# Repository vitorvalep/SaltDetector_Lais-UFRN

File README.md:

# SaltDetector_Lais-UFRN

Projeto foi feito como parte da seleção para bolsista do Laboratório de Inovação Tecnológica em Saúde.
Este projeto consiste em um hardware capaz de identificar a presença de sal ou açúcar em água. Para isso o projeto foi dividido em 4 partes

1 - Simulação de parte do projeto utilizando a ferramenta tinkerCAD e plataforma arduino

2 - Codificação do firmware utilizando a plataforma Arduino

3 - Desenvolvimento do hardware utilizando a ferramenta da autodesk Eagle.

4 - Desenvolvimento de case de proteção do hardware

## O projeto da placa de circuito impresso contém:

1 - Microcontrolador atmega328p, sendo o cérebro do sistema.

2 - Amplificadores operacionais para amplificação do sinal medido pelos eletrodos. Estes circuitos devem ser alterados durante calibração e testes.

3 - Suporte para cartão SD para que os dados sejam salvos em csv para análises posteriores.

4 - RTC para manter o horário atualizado e fazer o controle dos arquivos salvos no SD card

5 - Sistema de carregamento e utilização de baterias do tipo Lithium ion.

6 - Sensor de corrente I²C para medição de corrente para medição de corrente nos eletrodos.

7 - Display LCD 16x2 para visualização de informações dos sensores.

O Hardware desenvolvido é capaz de medir a condutividade da água por meio de uma célula formada por 3 eletrodos. Para a medição da condutividade, utilizou-se amplificadores operacionais para amplificar o sinal medido pelos eletrodos. A informação de que existe sal ou açúcar na água se dá por meio de um lcd 16x2, que mostra a condutividade da água e se há sal ou açúcar no mesmo. O dispositivo funciona com bateria do tipo Lithium ion e pode ser recarregado por uma entrada micro USB.

O dispositivo também é capaz de realizar a voltametria cíclica, experimento que consiste em enviar uma onda triangular de tensão e observar os valores de tensão e corrente nos eletrodos da célula Por meio do sensor de corrente embutido no hardware pode-se medir a corrente que flui pelo eletrodo de trabalho e o conversor A/D do chip atmeg328p junto com os amplificadores operacionais obtém o valor da tensão sobre o eletrodo de referência e o eletrodo de trabalho. Após a varredura, duas informações são mostradas no LCD, que são os picos de corrente e tensão durante o experimento. Há um slot para cartão SD que guarda todos os valores em um arquivo csv, cujo nome é a data e horário da voltametria. Com esse arquivo pode-se exportar as informações e gerar gráficos para análises posteriores

## Melhorias para o projeto.

1 - Utilizar de um display TFT touch para plotar gráficos e mostrar mais informações sobre a voltametria cíclica, bem como melhorar a interação entre o operador e hardware

2 - Utilizar um chip de comunicação GSM para que os dados sejam enviados em tempo real para a nuvem e lá contenha todas as informações coletadas pelo operador, eliminando assim, o uso do cartão SD.

3 - Melhorias do case de proteção da placa

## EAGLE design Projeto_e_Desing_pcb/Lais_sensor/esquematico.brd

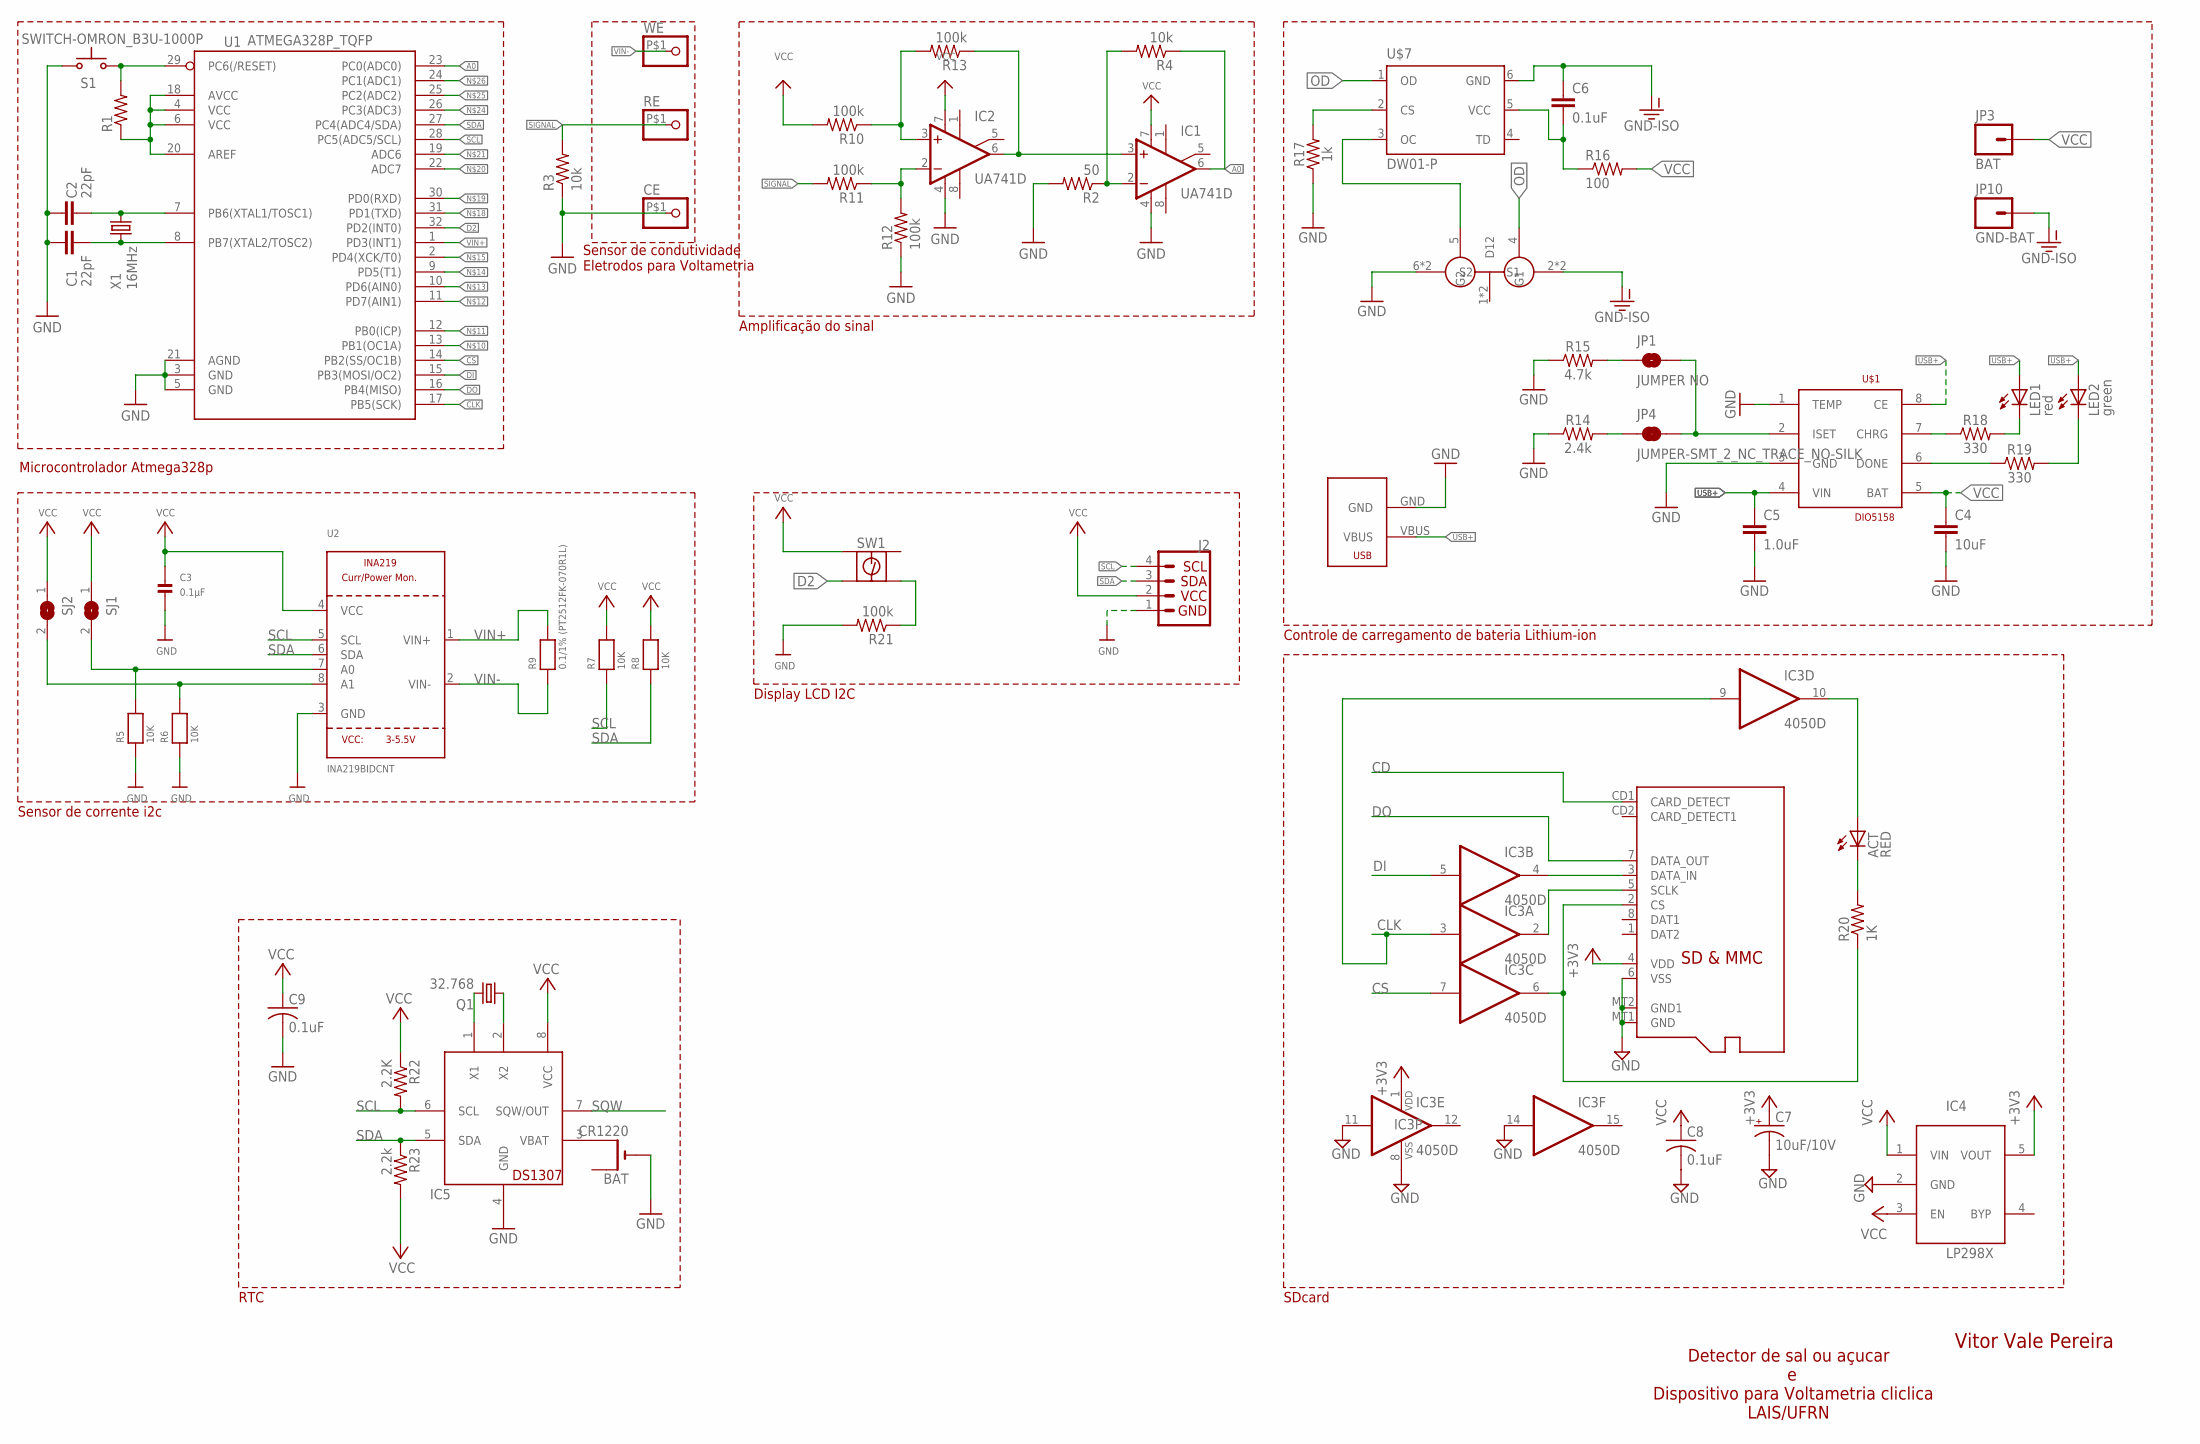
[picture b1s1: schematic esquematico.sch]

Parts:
ACT: RED; CHIP-LED0805
BAT: CR1220; CR1220-THM
C1, C2: 22pF; CAPM6032X280
C3: 0.1µF; 0805
C4: 10uF; 1206
C5: 1.0uF; 0603
C6: 0.1uF; 0603
C7: 10uF/10V; A/3216-18R
C8: 0.1uF; C0805K
C9: 0.1uF; C025-025X050
CE: PINHD-1X1-BIGPOGO; 1X1-BIGPOGO
IC1, IC2: UA741D; SO08
IC3: 4050D; SO16
IC4: LP298XS; SOT23-5L
IC5: DS1307; DIL08
J2: I2C_STANDARD; 1X04
JP1: JUMPER NO; SMT-JUMPER_2_NO_NO-SILK
JP3: BAT; 1X01
JP4: JUMPER-SMT_2_NC_TRACE_NO-SILK; SMT-JUMPER_2_NC_TRACE_NO-SILK
JP10: GND-BAT; 1X01
LED1: red; CHIP-LED0805
LED2: green; CHIP-LED0805
Q1: 32.768; TC38H
R1: R-US_R0805; R0805
R2: 50; R0805
R3, R4: 10k; R0805
R5, R6, R7, R8: 10K; 0805
R9: 0.1/1% (PT2512FK-070R1L); 2512
R10, R11, R12, R13, R21: 100k; R0805
R14: 2.4k; 0603
R15: 4.7k; 0603
R16: 100; 0603-RES
R17: 1k; 0603
R18, R19: 330; 0603
R20: 1K; R0805
R22: 2.2K; 0207/10
R23: 2.2k; 0207/10
RE: PINHD-1X1-BIGPOGO; 1X1-BIGPOGO
S1: SWITCH-OMRON_B3U-1000P
SJ1, SJ2: SOLDERJUMPERREFLOW_NOPASTE; SOLDERJUMPER_REFLOW_NOPASTE
SW1: PTS645SM43SMTR92LFS; PTS645-SMT-6MM
U1: ATMEGA328P_TQFP; TQFP32-08
U2: INA219BIDCNT; SOT23-8
U$1: DIO5158; SOIC-8
U$7: DW01-P; SOT23-6L
U$8: FS8205A; TSSOP8
U$9: USB-MICROB-POWERONLY
WE: PINHD-1X1-BIGPOGO; 1X1-BIGPOGO
X1: 16MHz; XTAL_HC49
X2: MICROSD

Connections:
+3V3: C7.+, IC3.1 (VDD), IC4.5 (VOUT), X2.4 (VDD)
A0: IC1.6 (OUT), R4.1, U1.23 (PC0(ADC0))
CD: X2.CD1 (CARD_DETECT)
CHRG: R18.1, U$1.7 (CHRG)
CLK: IC3.3 (I), IC3.9 (I), U1.17 (PB5(SCK))
CS: IC3.7 (I), U1.14 (PB2(SS/OC1B))
D2: SW1.P$3 (3), U1.32 (PD2(INT0))
DI: IC3.5 (I), U1.15 (PB3(MOSI/OC2))
DO: U1.16 (PB4(MISO)), X2.7 (DATA_OUT)
DONE: R19.1, U$1.6 (DONE)
GND: BAT.-, C1.1, C2.1, C3.2, C4.2, C5.2, C7.-, C8.2, C9.2, CE.P$1, IC1.4 (V-), IC2.4 (V-), IC3.8 (VSS), IC3.11 (I), IC3.14 (I), IC4.2 (GND), IC5.4 (GND), J2.1, R2.2, R3.1, R5.1, R6.1, R12.1, R14.1, R15.1, R17.1, R21.2, S1.1, U1.3 (GND), U1.5 (GND), U1.21 (AGND), U2.3 (GND), U$1.1 (TEMP), U$1.3 (GND), U$8.6 (S2), U$8.7 (S2), U$9.GND, X2.6 (VSS), X2.MT1 (GND), X2.MT2 (GND1)
GND-ISO: C6.1, JP10.1, U$7.6 (GND), U$8.2 (S1), U$8.3 (S1)
ISET: JP1.2, JP4.2, U$1.2 (ISET)
LED1: LED1.C, R18.2
LED2: LED2.C, R19.2
unnamed: C2.2, U1.7 (PB6(XTAL1/TOSC1)), X1.2
unnamed: C1.2, U1.8 (PB7(XTAL2/TOSC2)), X1.1
unnamed: R1.2, S1.2 (S), U1.29 (PC6(/RESET))
unnamed: IC1.2 (-IN), R2.1, R4.2
unnamed: R21.1, SW1.P$4 (4)
unnamed: R6.2, SJ2.2, U2.8 (A1)
unnamed: IC5.1 (X1), Q1.2
unnamed: IC2.3 (+IN), R10.1, R13.2
unnamed: IC5.2 (X2), Q1.1
unnamed: IC2.2 (-IN), R11.1, R12.2
unnamed: IC1.3 (+IN), IC2.6 (OUT), R13.1
unnamed: R5.2, SJ1.2, U2.7 (A0)
unnamed: JP4.1, R14.2
unnamed: JP1.1, R15.2
unnamed: R17.2, U$7.2 (CS)
unnamed: U$7.3 (OC), U$8.5 (G2)
unnamed: ACT.A, IC3.10 (O)
unnamed: IC3.2 (O), X2.5 (SCLK)
unnamed: IC3.6 (O), R20.1, X2.2 (CS)
unnamed: ACT.C, R20.2
unnamed: IC3.4 (O), X2.3 (DATA_IN)
unnamed: BAT.+2 (+1), IC5.3 (VBAT)
OD: U$7.1 (OD), U$8.4 (G1)
SCL: IC5.6 (SCL), J2.4, R7.1, R22.2, U1.28 (PC5(ADC5/SCL)), U2.5 (SCL)
SDA: IC5.5 (SDA), J2.3, R8.1, R23.1, U1.27 (PC4(ADC4/SDA)), U2.6 (SDA)
SIGNAL: R3.2, R11.2, RE.P$1
SQW: IC5.7 (SQW/OUT)
USB+: C5.1, LED1.A, LED2.A, U$1.4 (VIN), U$1.8 (CE), U$9.VBUS
VCC: C3.1, C4.1, C8.1, C9.1, IC1.7 (V+), IC2.7 (V+), IC4.1 (VIN), IC4.3 (EN), IC5.8 (VCC), J2.2, JP3.1, R1.1, R7.2, R8.2, R10.2, R16.2, R22.1, R23.2, SJ1.1, SJ2.1, SW1.P$1 (1), U1.4 (VCC), U1.6 (VCC), U1.18 (AVCC), U1.20 (AREF), U2.4 (VCC), U$1.5 (BAT)
VCC-DW: C6.2, R16.1, U$7.5 (VCC)
VIN+: R9.2, U1.1 (PD3(INT1)), U2.1 (VIN+)
VIN-: R9.1, U2.2 (VIN-), WE.P$1

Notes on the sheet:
Sensor de condutividade Eletrodos para Voltametria
Sensor de corrente i2c
Amplificação do sinal
Microcontrolador Atmega328p
Controle de carregamento de bateria Lithium-ion
SDcard
Display LCD I2C
RTC
Vitor Vale Pereira
Detector de sal ou açucar e Dispositivo para Voltametria cliclica LAIS/UFRN

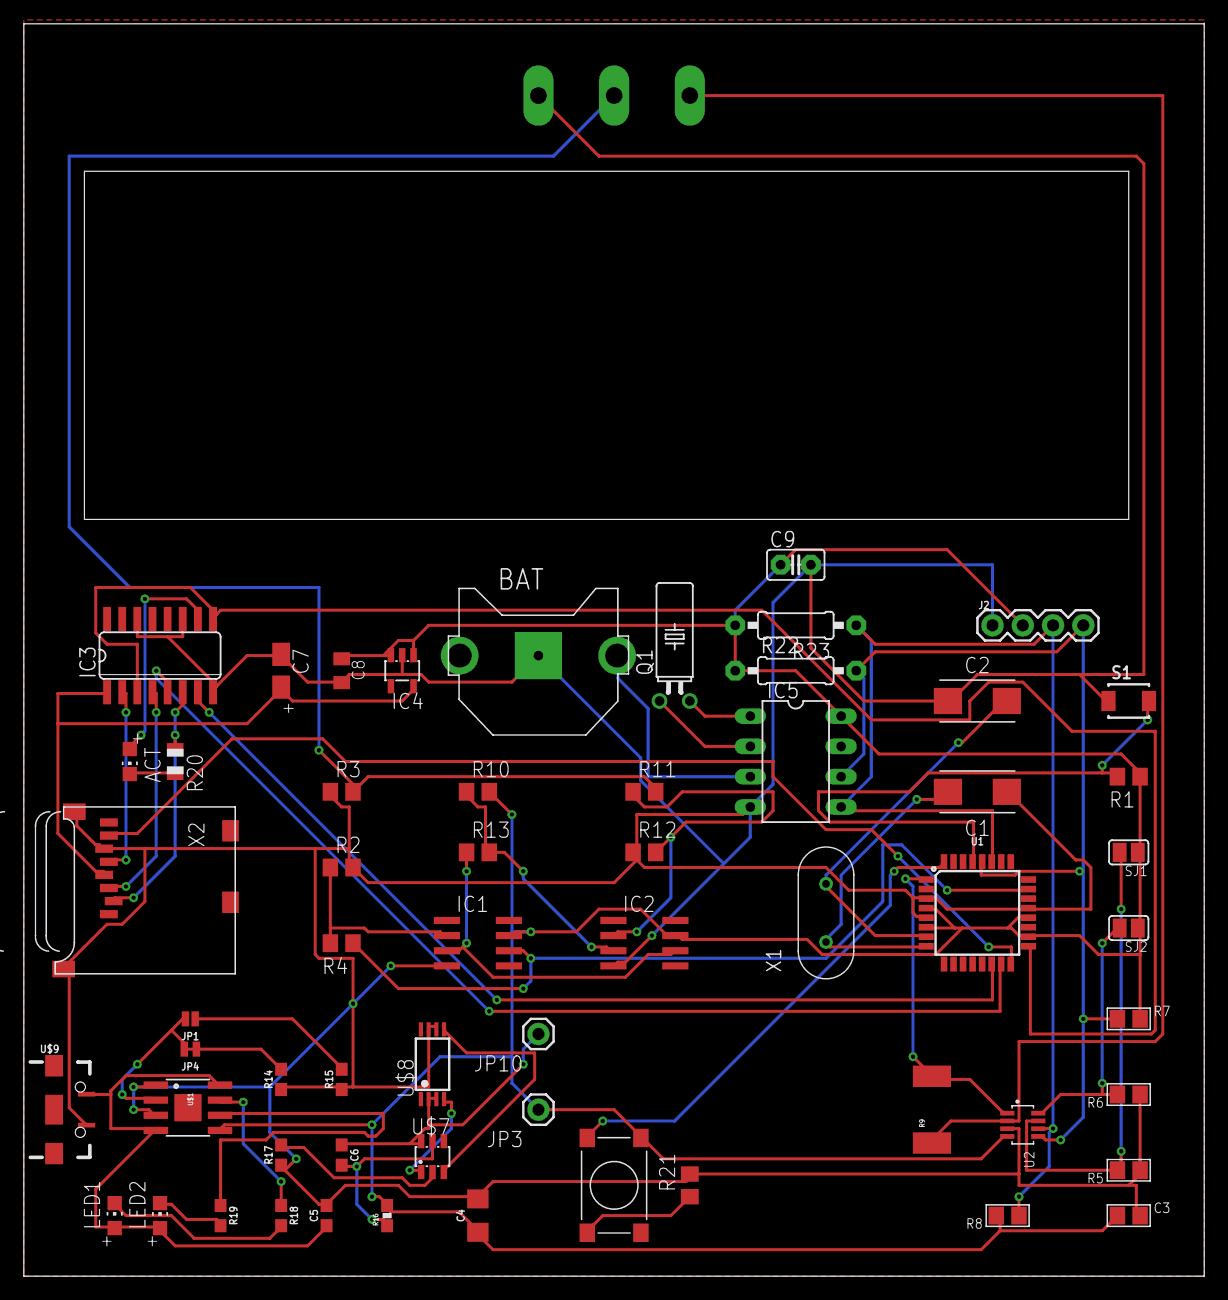
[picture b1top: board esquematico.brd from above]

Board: 2 copper layers, 99.0 x 105.1 mm, 62 parts (0 on the bottom side), 45 nets.

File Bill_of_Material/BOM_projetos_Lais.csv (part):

"Part";"Value";"Device";"Package";"Description";"CATEGORY";"CREATED_BY";"LABEL";"MANUFACTURER";"MPN";"OPERATING_TEMP";"PACKAGE";"PART_STATUS";"POPULARITY";"PROD_ID";"ROHS_COMPLIANT";"SERIES";"SPICEPREFIX";"SUB-CATEGORY";"THERMALLOSS";"TYPE";"VALUE";"VOLTAGE_RATING";
"ACT";"RED";"LEDCHIP-LED0805";"CHIP-LED0805";"LED";"";"";"";"";"";"";"";"";"";"";"";"";"";"";"";"";"";"";
"BAT";"CR1220";"CR1220THM";"CR1220-THM";"CR1216/CR1220/CR1225 12mm 3V lithium coin cell";"";"";"";"";"";"";"";"";"";"";"";"";"";"";"";"";"";"";
"C1";"22pF";"C_TANTALUM-2412(6032-METRIC)";"CAPM6032X280";"Capacitor - Generic";"Capacitor";"";"";"";"";"";"";"";"";"";"";"";"";"";"";"";"";"";
"C2";"22pF";"C_TANTALUM-2412(6032-METRIC)";"CAPM6032X280";"Capacitor - Generic";"Capacitor";"";"";"";"";"";"";"";"";"";"";"";"";"";"";"";"";"";
"C3";"0.1µF";"CAP_CERAMIC0805";"0805";"Ceramic Capacitors";"";"";"";"";"";"";"";"";"";"";"";"";"";"";"";"";"";"";
"C4";"10uF";"10UF-1206-6.3V-20%";"1206";"10.0µF ceramic capacitors";"";"";"";"";"";"";"";"";"";"CAP-10057";"";"";"";"";"";"";"10uF";"";
"C5";"1.0uF";"1.0UF-0603-16V-10%";"0603";"1µF ceramic capacitors";"";"";"";"";"";"";"";"";"";"CAP-00868";"";"";"";"";"";"";"1.0uF";"";
"C6";"0.1uF";"0.1UF-0603-25V-5%";"0603";"0.1µF ceramic capacitors";"";"";"";"";"";"";"";"";"";"CAP-08604";"";"";"";"";"";"";"0.1uF";"";
"C7";"10uF/10V";"CPOL-USA/3216-18R";"A/3216-18R";"POLARIZED CAPACITOR, American symbol";"";"";"";"";"";"";"";"";"";"";"";"";"";"";"";"";"";"";
"C8";"0.1uF";"C-USC0805K";"C0805K";"CAPACITOR, American symbol";"";"";"";"";"";"";"";"";"";"";"";"";"";"";"";"";"";"";
"C9";"0.1uF";"C-US025-025X050";"C025-025X050";"CAPACITOR, American symbol";"";"";"";"";"";"";"";"";"";"";"";"";"";"";"";"";"";"";
"CE";"";"PINHD-1X1-BIGPOGO";"1X1-BIGPOGO";"Pin header 1x1 for 0.1" spacing";"";"";"";"";"";"";"";"";"";"";"";"";"";"";"";"";"";"";
"IC1";"UA741D";"UA741D";"SO08";"OP AMP";"";"";"";"";"";"";"";"";"0";"";"";"";"";"";"";"";"";"";
"IC2";"UA741D";"UA741D";"SO08";"OP AMP";"";"";"";"";"";"";"";"";"0";"";"";"";"";"";"";"";"";"";
"IC3";"4050D";"4050D";"SO16";"Hex non-inverting BUFFER";"";"";"";"";"";"";"";"";"";"";"";"";"";"";"";"";"";"";
"IC4";"LP298XS";"LP298XS";"SOT23-5L";"";"";"";"";"";"";"";"";"";"";"";"";"";"";"";"";"";"";"";
"IC5";"DS1307";"DS1307";"DIL08";"DS1307";"";"";"";"";"";"";"";"";"";"";"";"";"";"";"";"";"";"";
"J2";"";"I2C_STANDARD";"1X04";"SparkFun I2C Standard Pinout Header";"";"";"";"";"";"";"";"";"";"";"";"";"";"";"";"";"";"";
"JP1";"JUMPER NO";"JUMPER-SMT_2_NO_NO-SILK";"SMT-JUMPER_2_NO_NO-SILK";"Normally open jumper";"";"";"";"";"";"";"";"";"";"";"";"";"";"";"";"";"";"";
"JP3";"BAT";"M01PTH";"1X01";"Header 1";"";"";"";"";"";"";"";"";"";"";"";"";"";"";"";"";"";"";
"JP4";"JUMPER-SMT_2_NC_TRACE_NO-SILK";"JUMPER-SMT_2_NC_TRACE_NO-SILK";"SMT-JUMPER_2_NC_TRACE_NO-SILK";"Normally closed trace jumper";"";"";"";"";"";"";"";"";"";"";"";"";"";"";"";"";"";"";
"JP10";"GND-BAT";"M01PTH";"1X01";"Header 1";"";"";"";"";"";"";"";"";"";"";"";"";"";"";"";"";"";"";
"LED1";"red";"LEDCHIP-LED0805";"CHIP-LED0805";"LED";"";"";"";"";"";"";"";"";"";"";"";"";"";"";"";"";"";"";
"LED2";"green";"LEDCHIP-LED0805";"CHIP-LED0805";"LED";"";"";"";"";"";"";"";"";"";"";"";"";"";"";"";"";"";"";
"Q1";"32.768";"CRYTALTC38H";"TC38H";"CRYSTAL";"";"";"";"";"";"";"";"";"";"";"";"";"";"";"";"";"";"";
"R1";"";"R-US_R0805";"R0805";"RESISTOR, American symbol";"";"";"";"";"";"";"";"";"";"";"";"";"R";"";"";"";"";"";
"R2";"50";"R-US_R0805";"R0805";"RESISTOR, American symbol";"";"";"";"";"";"";"";"";"";"";"";"";"R";"";"";"";"";"";
"R3";"10k";"R-US_R0805";"R0805";"RESISTOR, American symbol";"";"";"";"";"";"";"";"";"";"";"";"";"R";"";"";"";"";"";
"R4";"10k";"R-US_R0805";"R0805";"RESISTOR, American symbol";"";"";"";"";"";"";"";"";"";"";"";"";"R";"";"";"";"";"";
"R5";"10K";"RESISTOR0805";"0805";"Resistors";"";"";"";"";"";"";"";"";"";"";"";"";"";"";"";"";"";"";
"R6";"10K";"RESISTOR0805";"0805";"Resistors";"";"";"";"";"";"";"";"";"";"";"";"";"";"";"";"";"";"";
"R7";"10K";"RESISTOR0805";"0805";"Resistors";"";"";"";"";"";"";"";"";"";"";"";"";"";"";"";"";"";"";
"R8";"10K";"RESISTOR0805";"0805";"Resistors";"";"";"";"";"";"";"";"";"";"";"";"";"";"";"";"";"";"";
"R9";"0.1/1% (PT2512FK-070R1L)";"RESISTOR2512";"2512";"Resistors";"";"";"";"";"";"";"";"";"";"";"";"";"";"";"";"";"";"";
"R10";"100k";"R-US_R0805";"R0805";"RESISTOR, American symbol";"";"";"";"";"";"";"";"";"";"";"";"";"R";"";"";"";"";"";
"R11";"100k";"R-US_R0805";"R0805";"RESISTOR, American symbol";"";"";"";"";"";"";"";"";"";"";"";"";"R";"";"";"";"";"";
"R12";"100k";"R-US_R0805";"R0805";"RESISTOR, American symbol";"";"";"";"";"";"";"";"";"";"";"";"";"R";"";"";"";"";"";
"R13";"100k";"R-US_R0805";"R0805";"RESISTOR, American symbol";"";"";"";"";"";"";"";"";"";"";"";"";"R";"";"";"";"";"";
"R14";"2.4k";"2.49KOHM-0603-1/10W-1%";"0603";"2.49kΩ resistor";"";"";"";"";"";"";"";"";"";"RES-09568";"";"";"";"";"";"";"2.49k";"";
"R15";"4.7k";"4.7KOHM-0603-1/10W-1%";"0603";"4.7kΩ resistor";"";"";"";"";"";"";"";"";"";"RES-07857";"";"";"";"";"";"";"4.7k";"";
"R16";"100";"RESISTOR0603-RES";"0603-RES";"Resistor";"";"";"";"";"";"";"";"";"";"";"";"";"";"";"";"";"";"";
"R17";"1k";"1KOHM-0603-1/10W-1%";"0603";"1kΩ resistor";"";"";"";"";"";"";"";"";"";"RES-07856";"";"";"";"";"";"";"1k";"";
"R18";"330";"330OHM-0603-1/10W-1%";"0603";"330Ω resistor";"";"";"";"";"";"";"";"";"";"RES-00818";"";"";"";"";"";"";"330";"";
"R19";"330";"330OHM-0603-1/10W-1%";"0603";"330Ω resistor";"";"";"";"";"";"";"";"";"";"RES-00818";"";"";"";"";"";"";"330";"";
"R20";"1K";"R-US_R0805";"R0805";"RESISTOR, American symbol";"";"";"";"";"";"";"";"";"";"";"";"";"";"";"";"";"";"";
"R21";"100k";"R-US_R0805";"R0805";"RESISTOR, American symbol";"";"";"";"";"";"";"";"";"";"";"";"";"R";"";"";"";"";"";
"R22";"2.2K";"R-US_0207/10";"0207/10";"RESISTOR, American symbol";"";"";"";"";"";"";"";"";"";"";"";"";"";"";"";"";"";"";
"R23";"2.2k";"R-US_0207/10";"0207/10";"RESISTOR, American symbol";"";"";"";"";"";"";"";"";"";"";"";"";"";"";"";"";"";"";
"RE";"";"PINHD-1X1-BIGPOGO";"1X1-BIGPOGO";"Pin header 1x1 for 0.1" spacing";"";"";"";"";"";"";"";"";"";"";"";"";"";"";"";"";"";"";
"S1";"SWITCH-OMRON_B3U-1000P";"SWITCH-OMRON_B3U-1000P";"SWITCH-OMRON_B3U-1000P";"SMD Tactile Switch - Ultra Small";"";"";"";"";"";"";"";"";"";"";"";"";"";"";"";"";"";"";
"SJ1";"";"SOLDERJUMPERREFLOW_NOPASTE";"SOLDERJUMPER_REFLOW_NOPASTE";"SMD Solder JUMPER";"";"";"";"";"";"";"";"";"";"";"";"";"";"";"";"";"";"";
"SJ2";"";"SOLDERJUMPERREFLOW_NOPASTE";"SOLDERJUMPER_REFLOW_NOPASTE";"SMD Solder JUMPER";"";"";"";"";"";"";"";"";"";"";"";"";"";"";"";"";"";"";
"SW1";"PTS645SM43SMTR92LFS";"PTS645SM43SMTR92LFS";"PTS645-SMT-6MM";"SWITCH TACTILE SPST-NO 0.05A 12V";"";"";"";"";"";"";"";"";"";"";"";"";"";"";"";"";"";"";
"U$1";"DIO5158";"DIO5158";"SOIC-8";"";"";"";"";"";"";"";"";"";"";"";"";"";"";"";"";"";"";"";
"U$7";"DW01-P";"DW01-P";"SOT23-6L";"One Cell Lithium-ion/Polymer Battery Protection IC";"";"";"";"";"";"";"";"";"";"";"";"";"";"";"";"";"";"";
"U$8";"FS8205A";"FS8205A";"TSSOP8";"";"";"";"";"";"";"";"";"";"";"";"";"";"";"";"";"";"";"";
"U$9";"USB-MICROB-POWERONLY";"USB-MICROB-POWERONLY";"USB-MICROB-POWERONLY";"";"";"";"";"";"";"";"";"";"";"";"";"";"";"";"";"";"";"";
"U1";"ATMEGA328P_TQFP";"ATMEGA328P_TQFP";"TQFP32-08";"Popular 328P in QFP";"";"";"";"";"";"";"";"";"";"IC-09069";"";"";"";"";"";"";"ATMEGA328P_TQFP";"";
"U2";"INA219BIDCNT";"INA219";"SOT23-8";"INA219 - I2C Current/Power Monitor";"";"";"";"";"";"";"";"";"";"";"";"";"";"";"";"";"";"";
"WE";"";"PINHD-1X1-BIGPOGO";"1X1-BIGPOGO";"Pin header 1x1 for 0.1" spacing";"";"";"";"";"";"";"";"";"";"";"";"";"";"";"";"";"";"";
"X1";"16MHz";"49S/18PF";"XTAL_HC49";"Crystal";"";"PCBLayout.com";"";"Xinhunjing ";"49S/18PF";"";"SMD";"";"";"";"";"";"";"";"";"";"";"";
"X2";"MICROSD";"MICROSD";"MICROSD";"Micro-SD / Transflash card holder with SPI pinout";"";"";"";"";"";"";"";"";"";"";"";"";"";"";"";"";"";"";
"LCD1";"LCD-16X2NOSILK";"LCD-16X2NOSILK";"LCD-16X2_NOSILK";"Standard text-only 16x2 parallel input LCD";"LCD-00255";
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
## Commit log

2020-12-21 primeiro commit
2020-12-21 add case

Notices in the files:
parts and their libraries:
SparkFun-IC-Microcontroller: Licensing: Creative Commons ShareAlike 4.0 International - https://creativecommons.org/licenses/by-sa/4.0
SparkFun: Licensing: CC v3.0 Share-Alike You are welcome to use this library for commercial purposes.
